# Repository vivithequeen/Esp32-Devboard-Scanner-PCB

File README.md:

# I present... THE FULLS STACK DEVELOPMENT 2025-26 ESP32-C3-MINI-1 SCANNER BOARD!!!
## design stuff

| Component  | GPIO |
|------------|------|
| Green LED  | 2    |
| Red LED    | 18   |
| Transitior | 3    |
| RST        | 10   |
| IRQ        | NONE |
| MISO       | 6    |
| MOSI       | 4    |
| SCK        | 5    |
| SDA        | 7    |

## BOM
| Part name        | What is it               | How many | How many in the link | Price   | Price with Tax | Price Per Component |
|------------------|--------------------------|----------|----------------------|---------|----------------|---------------------|
| Buzzer           | 12x9.5 mm                | 1        | 20                   | $8.00   | $8.50          | $0.43               |
| Transistor       | 2N2222                   | 1        | 200                  | $6.99   | $7.43          | $0.04               |
| 100ohm Resistor  | we using 220 for safety  | 2        | 100                  | $5.49   | $5.83          | $0.06               |
| red led          |                          | 1        | 100                  | $12.99  | $13.80         | $0.14               |
| green led        |                          | 1        | 100                  | $12.99  | $13.80         | $0.14               |
| pcb              |                          | 1        | 1                    | $5.00   | $5.31          | $5.31               |
| devboard         | esp-32-c3-devkitm-1      | 1        | 1                    | $9.80   | $10.41         | $10.41              |
| pin headers      |                          | 4        | 50                   | $7.89   | $8.38          | $0.17               |
| MFRC522          | RFID SCANNER             | 1        | 1                    | $2.75   | $2.92          | $2.92               |
| JST Connector    |                          | 1        | 10                   | $8.99   | $9.55          | $0.96               |
| Case             |                          | 1        | 1                    | $2.20   | $2.34          | $2.34               |
|                  |                          | 0        | 1                    | $-      | $-             | $-                  |
|                  |                          | 0        | 1                    | $-      | $-             | $-                  |
|                  |                          | 0        | 1                    | $-      | $-             | $-                  |

**Total per pcb:** $23.47

here at some super awesome screenshots!!

traces diagaram

front silkscreens

back silkscreens

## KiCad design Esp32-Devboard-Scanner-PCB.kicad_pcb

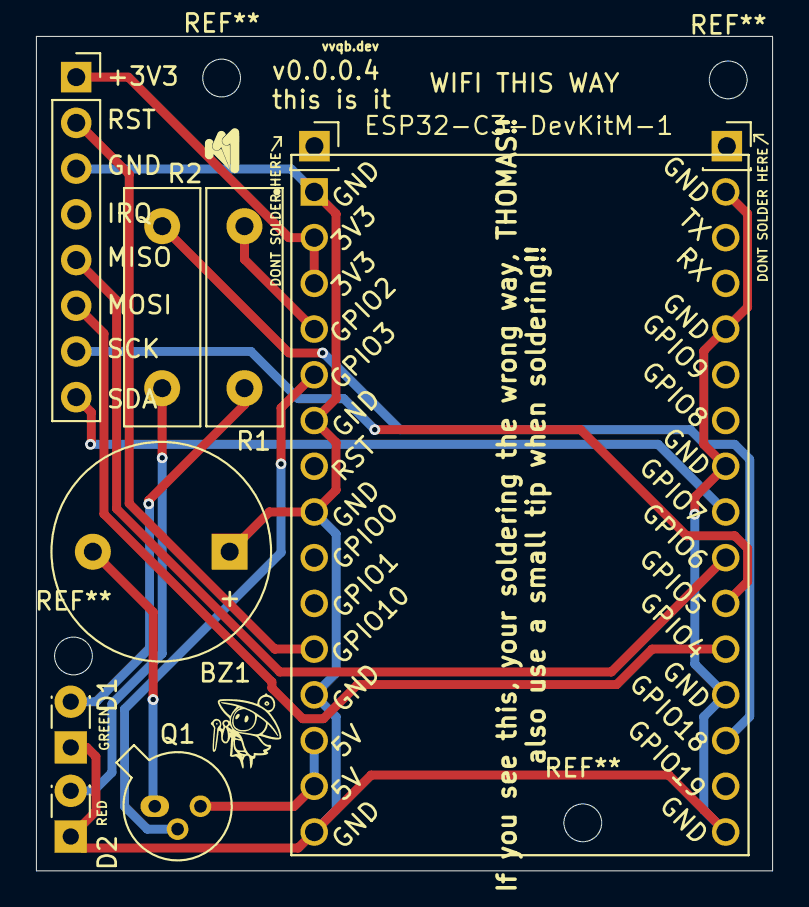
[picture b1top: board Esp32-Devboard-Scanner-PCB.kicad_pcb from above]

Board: 2 copper layers, 40.9 x 46.4 mm, 8 parts (0 on the bottom side), 14 nets.

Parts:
BZ1: Buzzer; Buzzer_12x9.5RM7.6
D1, D2: LED; LED_Rectangular_W3.0mm_H2.0mm
ESP32-C3-DevKitM-1: ESP32-C3-DEVKITM-1; XCVR_ESP32-C3-DEVKITM-1
J1: Conn_01x08_Pin; PinSocket_1x08_P2.54mm_Vertical
Q1: BC107; TO-18-3
R1: 100; R_Box_L13.0mm_W4.0mm_P9.00mm
R2: R; R_Box_L13.0mm_W4.0mm_P9.00mm

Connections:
5V: ESP32-C3-DevKitM-1.13 (5V), ESP32-C3-DevKitM-1.14 (5V), Q1.3 (C)
+3V3: ESP32-C3-DevKitM-1.2 (3V3), ESP32-C3-DevKitM-1.3 (3V3), J1.1
GND: BZ1.1 (+), D1.1 (K), D2.1 (K), ESP32-C3-DevKitM-1.1 (GND), ESP32-C3-DevKitM-1.6 (GND), ESP32-C3-DevKitM-1.8 (GND), ESP32-C3-DevKitM-1.12 (GND), ESP32-C3-DevKitM-1.15 (GND), ESP32-C3-DevKitM-1.16 (GND), ESP32-C3-DevKitM-1.19 (GND), ESP32-C3-DevKitM-1.24 (GND), ESP32-C3-DevKitM-1.27 (GND), ESP32-C3-DevKitM-1.30 (GND), J1.3
GPIO3: ESP32-C3-DevKitM-1.5 (IO3), Q1.2 (B)
GPIO4: ESP32-C3-DevKitM-1.20 (IO4), J1.6
GPIO5: ESP32-C3-DevKitM-1.21 (IO5), J1.7
GPIO6: ESP32-C3-DevKitM-1.22 (IO6), J1.5
GPIO7: ESP32-C3-DevKitM-1.23 (IO7), J1.8
GPIO10: ESP32-C3-DevKitM-1.11 (IO10), J1.2
unnamed: BZ1.2 (-), Q1.1 (E)
unnamed: D1.2 (A), R1.1
unnamed: D2.2 (A), R2.1
unnamed: ESP32-C3-DevKitM-1.4 (IO2), R1.2
unnamed: ESP32-C3-DevKitM-1.18 (IO18), R2.2
